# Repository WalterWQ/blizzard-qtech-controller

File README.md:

# Blizzard QTech replacement controller

An open-source replacement main board for the **SUN (Snap-on) Blizzard QTech2** vehicle air-conditioning service machine.

The original controller (NXP LPC2148) failed in my machine: it powered up and clicked its relays, but the display only showed blocks and the buttons did nothing. Every other part of the machine — valves, compressor, vacuum pump, scale, sensors — still worked. Rather than scrap a working machine for one dead board, I designed a new controller from scratch that plugs into the original wiring harness.

> ⚠️ **Mains voltage.** The power board switches 230 V AC to the compressor, heater and valves. Only build, test or install it if you are competent to work on mains equipment. Disconnect the supply before touching anything. The machine also handles pressurised refrigerant — follow F-gas rules.

> Not affiliated with, endorsed by or supported by Snap-on or SUN. "SUN", "Snap-on" and "Blizzard" are used only to describe what this board is compatible with.

| Controller board (v3, 4-layer) | Power & relay board (v1.1, 2-layer) |
|---|---|
|  |  |

## How it's built

The design is split across **two boards joined by a 26-way ribbon cable**, so the low-voltage logic and the mains switching are kept apart. Either board can be repaired or replaced on its own.

```
                 ┌──────────────────────────┐   ribbon (J30)   ┌───────────────────────────┐
  keypad ───────►│     CONTROLLER BOARD     │◄────────────────►│   POWER & RELAY BOARD     │──► 10 × solenoid valves
  LCD    ◄───────│  ESP32-S3, sensors, I/O  │  relay drive,    │  230 V in, fused outputs  │──► compressor, vac pump
  sensors ──────►│  watchdog, RTC, FRAM     │  12 V, SAFE_EN,  │  transformer, 12 V / 5 V  │──► tank heater, fan
  printer ◄──────│                          │  E-stop, HP sw.  │  relays + varistors       │◄── E-stop, HP switch
                 └──────────────────────────┘                  └───────────────────────────┘
```

### Controller board (v3)

4-layer, 180 × 125 mm.

| Function | Part |
|---|---|
| Microcontroller | ESP32-S3-WROOM-1 (N8 or N16R8) — Wi-Fi, USB-C programming with ESD protection |
| Display | Original 14-pin HD44780 character LCD, via a 74HCT245 level shifter; backlight on a MOSFET |
| Keypad | Original keypad, scanned through an MCP23017 I/O expander |
| Pressure | 5 inputs for 0.5–4.5 V transducers (high side, low side, 2 × manifold, spare), each with TVS protection and a jumper-selectable sensor supply |
| Temperature | Tank NTC thermistor |
| Refrigerant scale | NAU7802 24-bit load-cell ADC |
| Current sensing | 2 × 3.5 mm jacks for CT clamps (compressor, vacuum pump) |
| Monitoring | 12 V and 5 V rail monitors, leak sensor — 3 × ADS1115 16-bit ADCs |
| Storage | MB85RC256V FRAM (32 KB) for settings and logs |
| Clock | DS3231M real-time clock with CR2032 backup |
| Safety | TPS3823 hardware watchdog AND-ed with a GPIO to produce `SAFE_EN` — if the firmware hangs, every output drops out |
| Printer | Original printer port, RS-232 (MAX3232) or TTL, jumper selectable |
| Extras | Buzzer, WS2812B status LED, second MCP23017 for expansion |

### Power & relay board (v1.1)

2-layer, 272 × 198 mm, 1 oz copper.

| Function | Detail |
|---|---|
| Mains input | EMI filter choke, X2/Y2 safety capacitors |
| Supplies | Hahn UI39 PCB transformer (reused from the original board) → bridge rectifiers → LM2937 12 V linear and LM2596 5 V buck regulators |
| Fusing | Separate 5×20 mm fuses for the transformer (T125 mA), valves (T2 A), motors (T6.3 A) and heater (T2 A); resettable fuses on the low-voltage side |
| Valve outputs | 10 × 230 V outputs for the Parker YB14 solenoid coils (14 W), each with a varistor |
| Motor outputs | Compressor (1/3 HP), vacuum pump and fan, with larger varistors |
| Heater output | 230 V, 230 W tank heater (optional parts — leave out if the machine has no heater) |
| Relays | 12 V coil relays driven by 2 × ULN2803A, with an LED per output. Footprints for Omron G2RL, plus the original Panasonic JW1FSN / ALZ22B12 relays reused from the old board |
| Safety inputs | E-stop and high-pressure switch (both normally closed) |
| Wiring | 7.62 mm mains screw terminals, labelled for each valve and motor |

Bills of materials: [controller](hardware/controller-board/BOM.csv) · [power board](hardware/power-board/BOM.csv) · [cable and extras](hardware/BOM_extras.csv)

## Repository layout

```
firmware/
  bench-test/AC_Controller_Test/   Bench-test firmware for the controller board
hardware/
  controller-board/                KiCad 10 project, BOM, gerbers (fabrication/), 1:1 fit-check print
  power-board/                     KiCad 10 project, BOM, gerbers, custom footprints and 3D models
  BOM_extras.csv                   Ribbon cable, jumpers and other loose parts
docs/images/                       Board renders
```

Open the `.kicad_pro` files in **KiCad 10** or newer. The gerber zips in each `fabrication/` folder can be uploaded to JLCPCB as they are.

## Bench-test firmware

[`firmware/bench-test`](firmware/bench-test/AC_Controller_Test/AC_Controller_Test.ino) checks a freshly built controller board on its own, powered from USB-C — no power board or mains needed. It uses no external libraries.

On power-up it runs automatic tests and shows the result on the LCD and status LED:

- Finds every I²C device (I/O expanders, ADCs, load-cell ADC, FRAM, RTC)
- FRAM write/read-back and boot counter
- RTC ticking and temperature
- 5 V, 12 V and sensor supply rails
- Load-cell ADC, Wi-Fi scan

Then a serial menu for hands-on tests: live sensor readings, keypad mapping, walking each relay output, backlight/buzzer/LED, the watchdog and `SAFE_EN` cut-out, printer-port loopback, load-cell readings and setting the clock.

**Arduino IDE setup:** board *ESP32S3 Dev Module*, *USB CDC On Boot: Enabled*, flash and PSRAM to match your module. Full steps are at the top of the sketch.

## Status

| Part | Status |
|---|---|
| Controller board v3 | ✅ Built and hand-soldered |
| Bench-test firmware | ✅ Written |
| Power & relay board v1.1 | 🛠️ Design finished, gerbers ready |
| Machine control firmware | 🔜 Next |

## Licence

- Firmware (`firmware/`): [MIT](LICENSE)
- Hardware (`hardware/`): [CERN-OHL-P v2](LICENSE-HARDWARE)

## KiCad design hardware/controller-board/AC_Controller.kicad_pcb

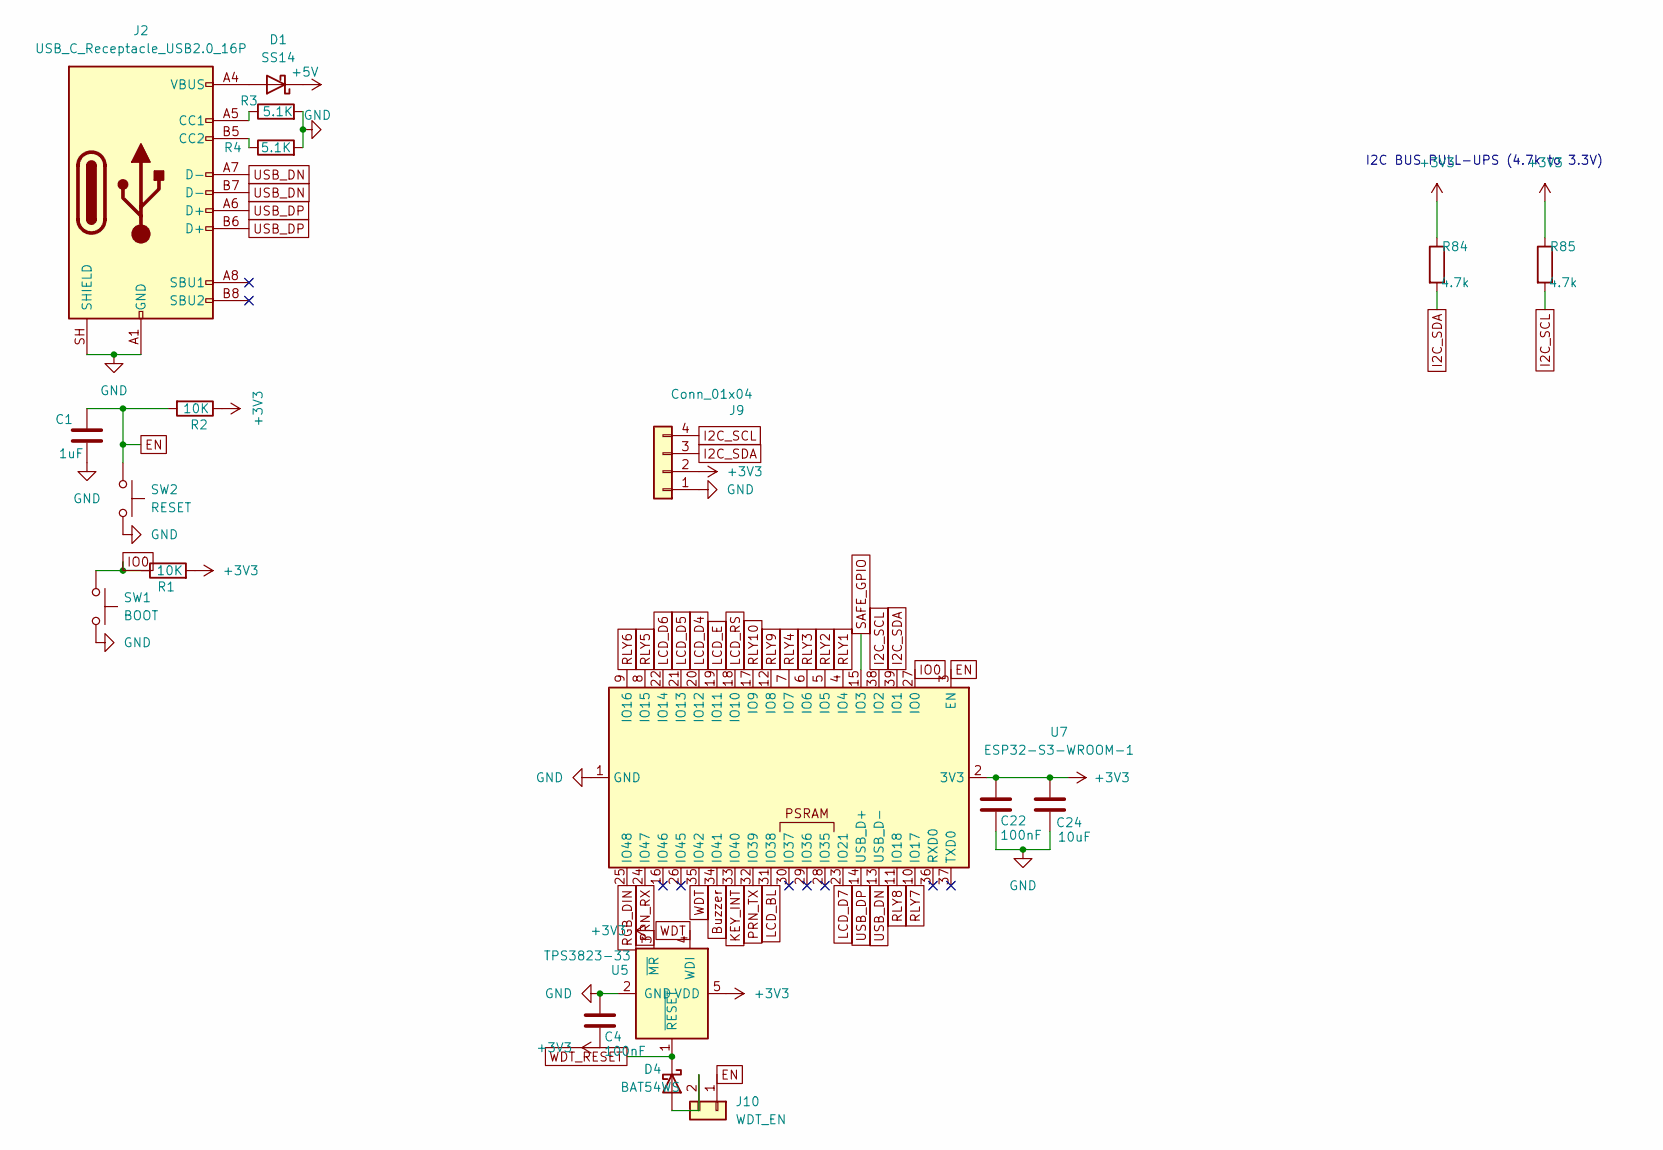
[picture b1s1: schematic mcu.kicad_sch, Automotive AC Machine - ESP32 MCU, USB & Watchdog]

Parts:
C1: 1uF; C_0805_2012Metric
C4, C22: 100nF; C_0805_2012Metric
C24: 10uF; C_0805_2012Metric
D1: SS14; D_SMA
D4: BAT54WS; D_SOD-323
J2: USB_C_Receptacle_USB2.0_16P; USB_C_Receptacle_HRO_TYPE-C-31-M-12
J9: Conn_01x04; PinHeader_1x04_P2.54mm_Vertical
J10: WDT_EN; PinHeader_1x02_P2.54mm_Vertical
R1, R2: 10K; R_0805_2012Metric
R3, R4: 5.1K; R_0805_2012Metric
R84, R85: 4.7k; R_0805_2012Metric
SW1: BOOT; SW_PUSH_6mm
SW2: RESET; SW_PUSH_6mm
U5: TPS3823-33; SOT-23-5
U7: ESP32-S3-WROOM-1

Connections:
+3V3: C4.2, C22.1, C24.1, J9.2, R1.2, R2.1, R84.1, R85.1, U5.3 (~MR), U5.5 (VDD), U7.2 (3V3); also elsewhere on the board
+5V: D1.1 (K); also elsewhere on the board
Buzzer: U7.34 (IO41); also elsewhere on the board
EN: C1.1, J10.1, R2.2, SW2.1, U7.3 (EN)
GND: C1.2, C4.1, C22.2, C24.2, J2.A1 (GND), J2.A12 (GND), J2.B1 (GND), J2.B12 (GND), J2.SH (SHIELD), J9.1, R3.2, R4.2, SW1.2, SW2.2, U5.2 (GND), U7.1 (GND), U7.40 (GND), U7.41 (GND); also elsewhere on the board
I2C_SCL: J9.4, R85.2, U7.38 (IO2); also elsewhere on the board
I2C_SDA: J9.3, R84.2, U7.39 (IO1); also elsewhere on the board
IO0: R1.1, SW1.1, U7.27 (IO0)
KEY_INT: U7.33 (IO40); also elsewhere on the board
LCD_BL: U7.31 (IO38); also elsewhere on the board
LCD_D4: U7.20 (IO12); also elsewhere on the board
LCD_D5: U7.21 (IO13); also elsewhere on the board
LCD_D6: U7.22 (IO14); also elsewhere on the board
LCD_D7: U7.23 (IO21); also elsewhere on the board
LCD_E: U7.19 (IO11); also elsewhere on the board
LCD_RS: U7.18 (IO10); also elsewhere on the board
unnamed: D1.2 (A), J2.A4 (VBUS), J2.A9 (VBUS), J2.B4 (VBUS), J2.B9 (VBUS)
unnamed: D4.2 (A), J10.2
unnamed: J2.A5 (CC1), R3.1
unnamed: J2.B5 (CC2), R4.1
PRN_RX: U7.24 (IO47); also elsewhere on the board
PRN_TX: U7.32 (IO39); also elsewhere on the board
RGB_DIN: U7.25 (IO48); also elsewhere on the board
RLY1: U7.4 (IO4); also elsewhere on the board
RLY2: U7.5 (IO5); also elsewhere on the board
RLY3: U7.6 (IO6); also elsewhere on the board
RLY4: U7.7 (IO7); also elsewhere on the board
RLY5: U7.8 (IO15); also elsewhere on the board
RLY6: U7.9 (IO16); also elsewhere on the board
RLY7: U7.10 (IO17); also elsewhere on the board
RLY8: U7.11 (IO18); also elsewhere on the board
RLY9: U7.12 (IO8); also elsewhere on the board
RLY10: U7.17 (IO9); also elsewhere on the board
SAFE_GPIO: U7.15 (IO3); also elsewhere on the board
USB_DN: J2.A7 (D-), J2.B7 (D-), U7.13 (USB_D-); also elsewhere on the board
USB_DP: J2.A6 (D+), J2.B6 (D+), U7.14 (USB_D+); also elsewhere on the board
WDT: U5.4 (WDI), U7.35 (IO42)
WDT_RESET: D4.1 (K), U5.1 (~RESET); also elsewhere on the board

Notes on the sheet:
I2C BUS PULL-UPS (4.7k to 3.3V)

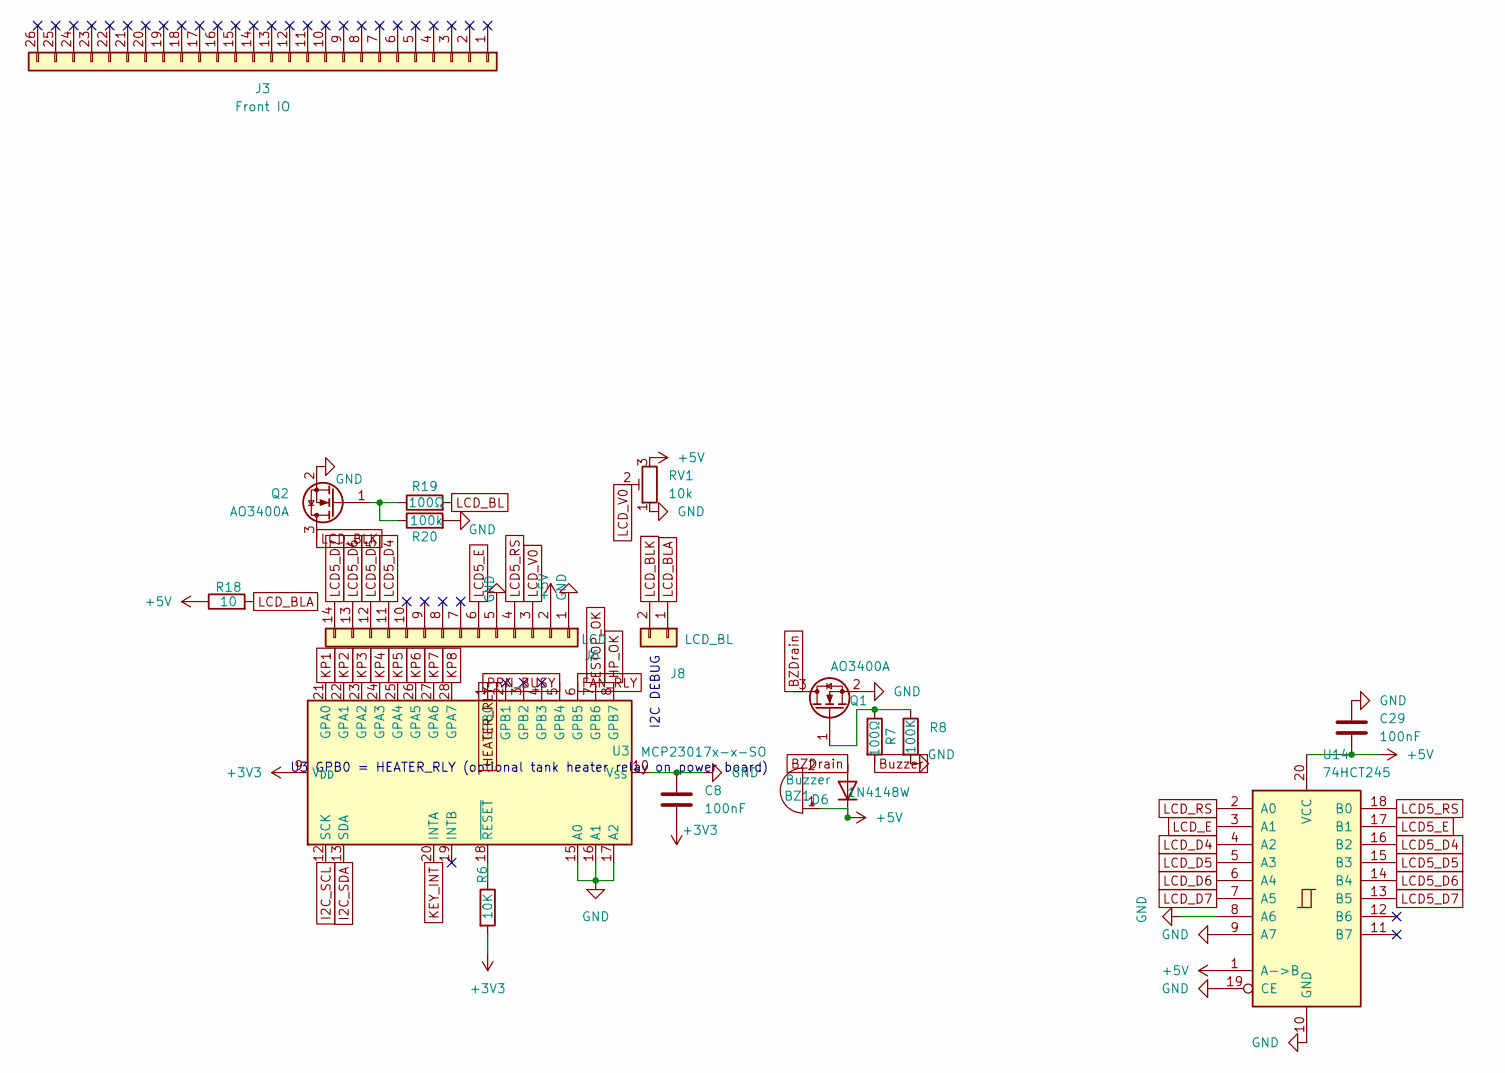
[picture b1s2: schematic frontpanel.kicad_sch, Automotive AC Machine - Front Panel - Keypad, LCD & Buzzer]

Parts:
BZ1: Buzzer; Buzzer_12x9.5RM7.6
C8, C29: 100nF; C_0805_2012Metric
D6: 1N4148W; D_SOD-123
J3: Front IO; PinHeader_1x26_P2.54mm_Vertical
J6: LCD; PinHeader_1x14_P2.54mm_Vertical
J8: LCD_BL; PinHeader_1x02_P2.54mm_Vertical
Q1, Q2: AO3400A; SOT-23
R6: 10K; R_0805_2012Metric
R7, R19: 100Ω; R_0805_2012Metric
R8: 100K; R_0805_2012Metric
R18: 10; R_0805_2012Metric
R20: 100k; R_0805_2012Metric
RV1: 10k; Potentiometer_Bourns_3296W_Vertical
U3: MCP23017x-x-SO; SOIC-28W_7.5x17.9mm_P1.27mm
U14: 74HCT245; SOIC-20W_7.5x12.8mm_P1.27mm

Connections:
+3V3: C8.1, R6.2, U3.9 (V_{DD}); also elsewhere on the board
+5V: BZ1.1 (+), C29.1, D6.1 (K), J6.2, R18.1, RV1.3, U14.1 (A->B), U14.20 (VCC); also elsewhere on the board
BZDrain: BZ1.2 (-), D6.2 (A), Q1.3 (D)
Buzzer: R7.2; also elsewhere on the board
ESTOP_OK: U3.7 (GPB6); also elsewhere on the board
FAN_RLY: U3.6 (GPB5); also elsewhere on the board
GND: C8.2, C29.2, J6.1, J6.5, Q1.2 (S), Q2.2 (S), R8.2, R20.2, RV1.1, U3.10 (V_{SS}), U3.15 (A0), U3.16 (A1), U3.17 (A2), U14.8 (A6), U14.9 (A7), U14.10 (GND), U14.19 (CE); also elsewhere on the board
HEATER_RLY: U3.1 (GPB0); also elsewhere on the board
HP_OK: U3.8 (GPB7); also elsewhere on the board
I2C_SCL: U3.12 (SCK); also elsewhere on the board
I2C_SDA: U3.13 (SDA); also elsewhere on the board
KEY_INT: U3.20 (INTA); also elsewhere on the board
KP1: U3.21 (GPA0); also elsewhere on the board
KP2: U3.22 (GPA1); also elsewhere on the board
KP3: U3.23 (GPA2); also elsewhere on the board
KP4: U3.24 (GPA3); also elsewhere on the board
KP5: U3.25 (GPA4); also elsewhere on the board
KP6: U3.26 (GPA5); also elsewhere on the board
KP7: U3.27 (GPA6); also elsewhere on the board
KP8: U3.28 (GPA7); also elsewhere on the board
LCD5_D4: J6.11, U14.16 (B2)
LCD5_D5: J6.12, U14.15 (B3)
LCD5_D6: J6.13, U14.14 (B4)
LCD5_D7: J6.14, U14.13 (B5)
LCD5_E: J6.6, U14.17 (B1)
LCD5_RS: J6.4, U14.18 (B0)
LCD_BL: R19.2; also elsewhere on the board
LCD_BLA: J8.1, R18.2
LCD_BLK: J8.2, Q2.3 (D)
LCD_D4: U14.4 (A2); also elsewhere on the board
LCD_D5: U14.5 (A3); also elsewhere on the board
LCD_D6: U14.6 (A4); also elsewhere on the board
LCD_D7: U14.7 (A5); also elsewhere on the board
LCD_E: U14.3 (A1); also elsewhere on the board
LCD_RS: U14.2 (A0); also elsewhere on the board
LCD_V0: J6.3, RV1.2
unnamed: Q1.1 (G), R7.1, R8.1
unnamed: Q2.1 (G), R19.1, R20.1
unnamed: R6.1, U3.18 (~RESET)
PRN_BUSY: U3.5 (GPB4); also elsewhere on the board

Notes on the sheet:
I2C DEBUG
U3 GPB0 = HEATER_RLY (optional tank heater relay on power board)

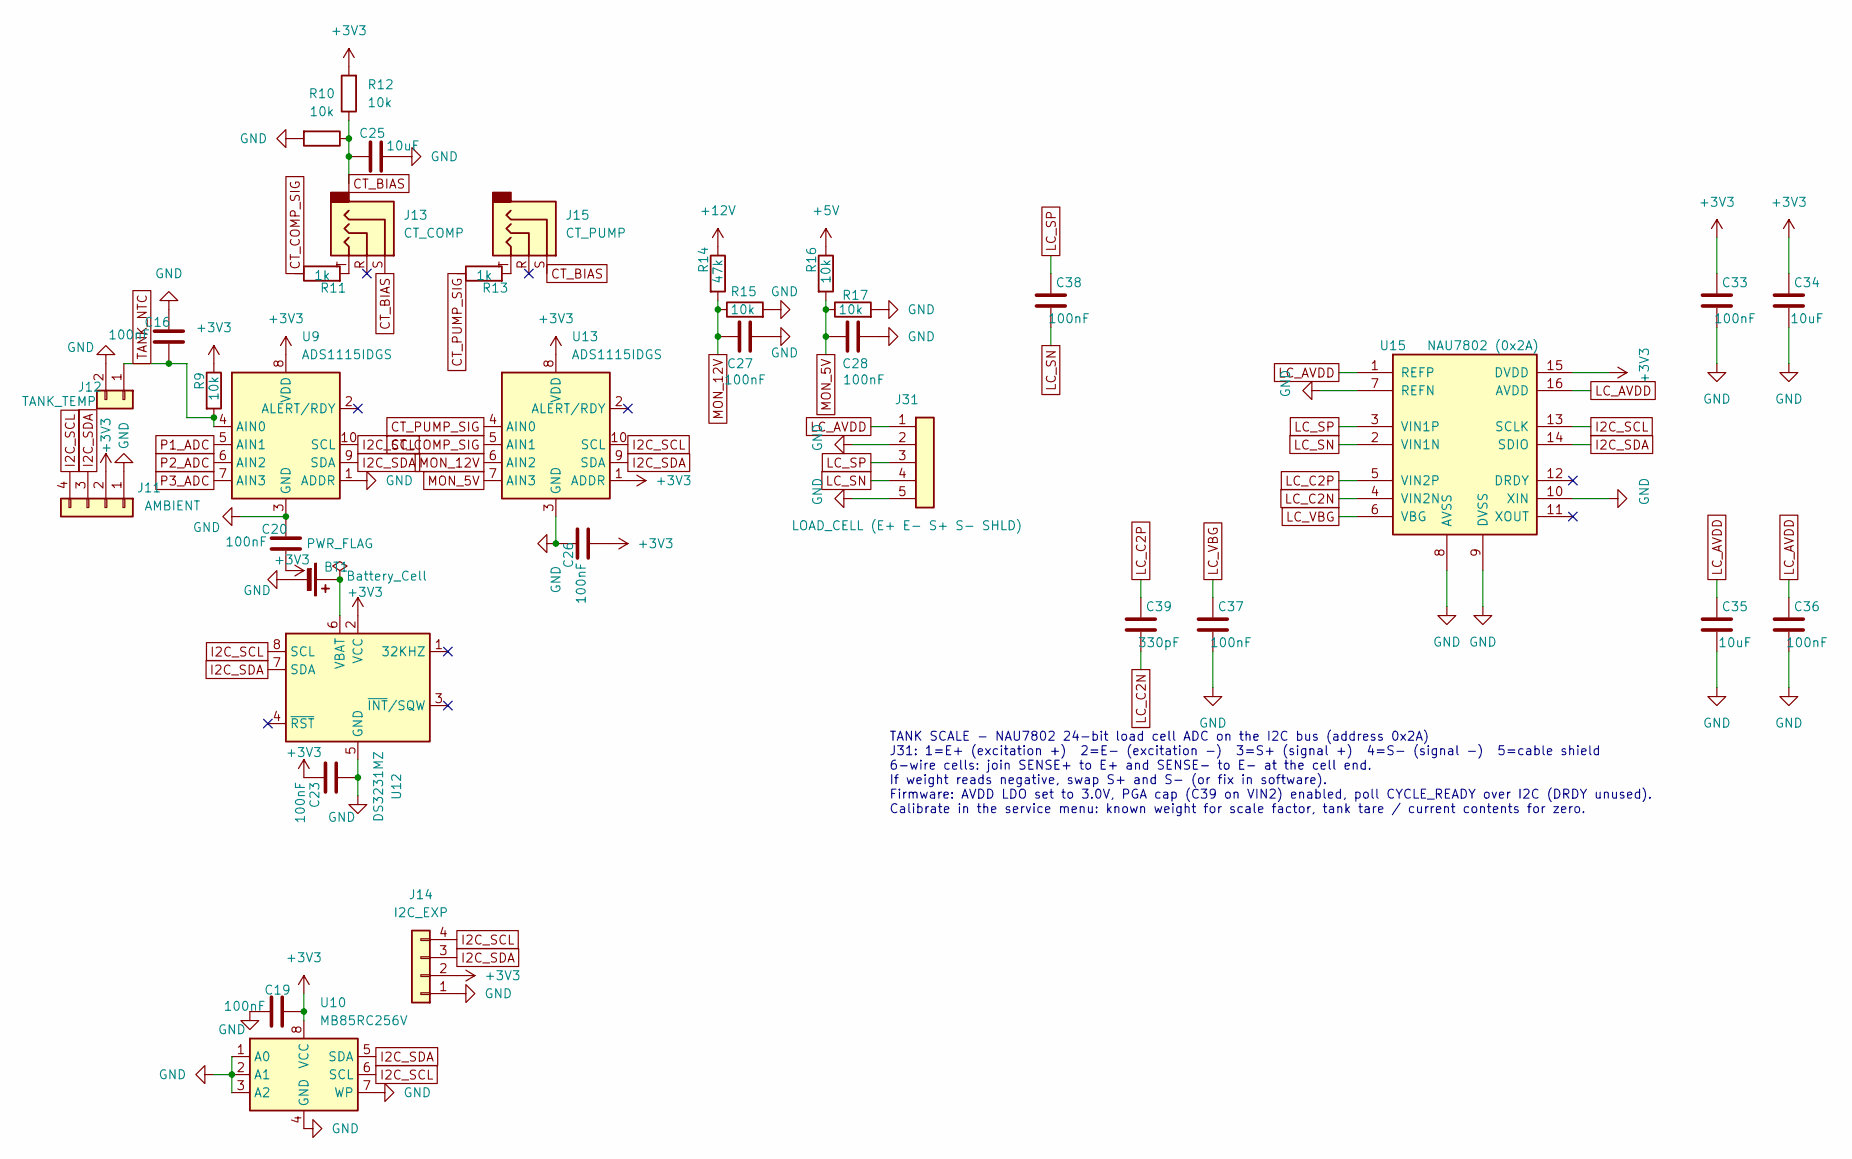
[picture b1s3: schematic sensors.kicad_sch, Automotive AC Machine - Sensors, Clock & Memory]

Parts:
BT1: Battery_Cell; BatteryHolder_Keystone_1058_1x2032
C16, C19, C20, C23, C26, C27, C28, C33, C36, C37, C38: 100nF; C_0805_2012Metric
C25, C34, C35: 10uF; C_0805_2012Metric
C39: 330pF; C_0805_2012Metric
J11: AMBIENT; PinHeader_1x04_P2.54mm_Vertical
J12: TANK_TEMP; TerminalBlock_Phoenix_MKDS-1,5-2-5.08_1x02_P5.08mm_Horizont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
J13: CT_COMP; Jack_3.5mm_CUI_SJ1-3533NG_Horizontal
J14: I2C_EXP; PinHeader_1x04_P2.54mm_Vertical
J15: CT_PUMP; Jack_3.5mm_CUI_SJ1-3533NG_Horizontal
J31: LOAD_CELL (E+ E- S+ S- SHLD); TerminalBlock_Phoenix_MKDS-1,5-5-5.08_1x05_P5.08mm_Horizont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
R9, R10, R12, R15, R16, R17: 10k; R_0805_2012Metric
R11, R13: 1k; R_0805_2012Metric
R14: 47k; R_0805_2012Metric
U9, U13: ADS1115IDGS; TSSOP-10_3x3mm_P0.5mm
U10: MB85RC256V; SOIC-8_3.9x4.9mm_P1.27mm
U12: DS3231MZ; SOIC-8_3.9x4.9mm_P1.27mm
U15: NAU7802 (0x2A); SOIC-16_3.9x9.9mm_P1.27mm

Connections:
+3V3: C19.2, C20.2, C23.2, C26.2, C33.1, C34.1, J11.2, J14.2, R9.1, R12.2, U9.8 (VDD), U10.8 (VCC), U12.2 (VCC), U13.1 (ADDR), U13.8 (VDD), U15.15 (DVDD); also elsewhere on the board
+5V: R16.1; also elsewhere on the board
+12V: R14.1; also elsewhere on the board
CT_BIAS: C25.1, J13.S, J15.S, R10.1, R12.1
CT_COMP_SIG: R11.1, U13.5 (AIN1); also elsewhere on the board
CT_PUMP_SIG: R13.1, U13.4 (AIN0); also elsewhere on the board
GND: BT1.2 (-), C16.1, C19.1, C20.1, C23.1, C25.2, C26.1, C27.2, C28.2, C33.2, C34.2, C35.2, C36.2, C37.2, J11.1, J12.2, J14.1, J31.2, J31.5, R10.2, R15.2, R17.2, U9.1 (ADDR), U9.3 (GND), U10.1 (A0), U10.2 (A1), U10.3 (A2), U10.4 (GND), U10.7 (WP), U12.5 (GND), U13.3 (GND), U15.7 (REFN), U15.8 (AVSS), U15.9 (DVSS), U15.10 (XIN); also elsewhere on the board
I2C_SCL: J11.4, J14.4, U9.10 (SCL), U10.6 (SCL), U12.8 (SCL), U13.10 (SCL), U15.13 (SCLK); also elsewhere on the board
I2C_SDA: J11.3, J14.3, U9.9 (SDA), U10.5 (SDA), U12.7 (SDA), U13.9 (SDA), U15.14 (SDIO); also elsewhere on the board
LC_AVDD: C35.1, C36.1, J31.1, U15.1 (REFP), U15.16 (AVDD)
LC_C2N: C39.2, U15.4 (VIN2N)
LC_C2P: C39.1, U15.5 (VIN2P)
LC_SN: C38.2, J31.4, U15.2 (VIN1N)
LC_SP: C38.1, J31.3, U15.3 (VIN1P)
LC_VBG: C37.1, U15.6 (VBG)
MON_5V: C28.1, R16.2, R17.1, U13.7 (AIN3)
MON_12V: C27.1, R14.2, R15.1, U13.6 (AIN2)
unnamed: BT1.1 (+), U12.6 (VBAT)
unnamed: J13.T, R11.2
unnamed: J15.T, R13.2
P1_ADC: U9.5 (AIN1); also elsewhere on the board
P2_ADC: U9.6 (AIN2); also elsewhere on the board
P3_ADC: U9.7 (AIN3); also elsewhere on the board
TANK_NTC: C16.2, J12.1, R9.2, U9.4 (AIN0); also elsewhere on the board

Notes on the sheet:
TANK SCALE - NAU7802 24-bit load cell ADC on the I2C bus (address 0x2A) J31: 1=E+ (excitation +) 2=E- (excitation -) 3=S+ (signal +) 4=S- (signal -) 5=cable shield 6-wire cells: join SENSE+ to E+ and SENSE- to E- at the cell end. If weight reads negative, swap S+ and S- (or fix in software). Firmwa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

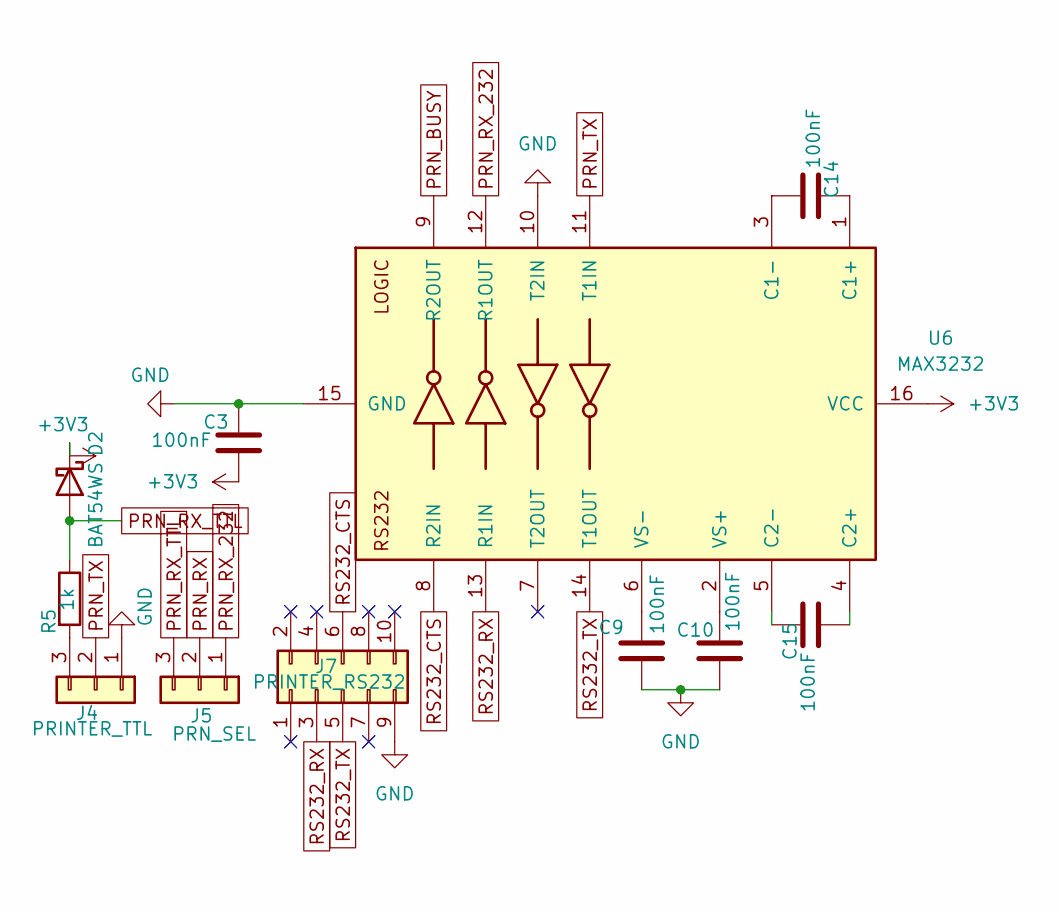
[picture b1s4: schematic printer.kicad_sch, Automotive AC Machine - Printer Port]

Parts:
C3, C9, C10, C14, C15: 100nF; C_0805_2012Metric
D2: BAT54WS; D_SOD-323
J4: PRINTER_TTL; PinHeader_1x03_P2.54mm_Vertical
J5: PRN_SEL; PinHeader_1x03_P2.54mm_Vertical
J7: PRINTER_RS232; IDC-Header_2x05_P2.54mm_Vertical
R5: 1k; R_0805_2012Metric
U6: MAX3232; SOIC-16_3.9x9.9mm_P1.27mm

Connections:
+3V3: C3.2, D2.1 (K), U6.16 (VCC); also elsewhere on the board
GND: C3.1, C9.2, C10.2, J4.1, J7.9, U6.10 (T2IN), U6.15 (GND); also elsewhere on the board
unnamed: J4.3, R5.2
unnamed: C14.1, U6.1 (C1+)
unnamed: C14.2, U6.3 (C1-)
unnamed: C15.2, U6.4 (C2+)
unnamed: C15.1, U6.5 (C2-)
unnamed: C10.1, U6.2 (VS+)
unnamed: C9.1, U6.6 (VS-)
PRN_BUSY: U6.9 (R2OUT); also elsewhere on the board
PRN_RX: J5.2; also elsewhere on the board
PRN_RX_232: J5.1, U6.12 (R1OUT)
PRN_RX_TTL: D2.2 (A), J5.3, R5.1
PRN_TX: J4.2, U6.11 (T1IN); also elsewhere on the board
RS232_CTS: J7.6, U6.8 (R2IN)
RS232_RX: J7.3, U6.13 (R1IN)
RS232_TX: J7.5, U6.14 (T1OUT)

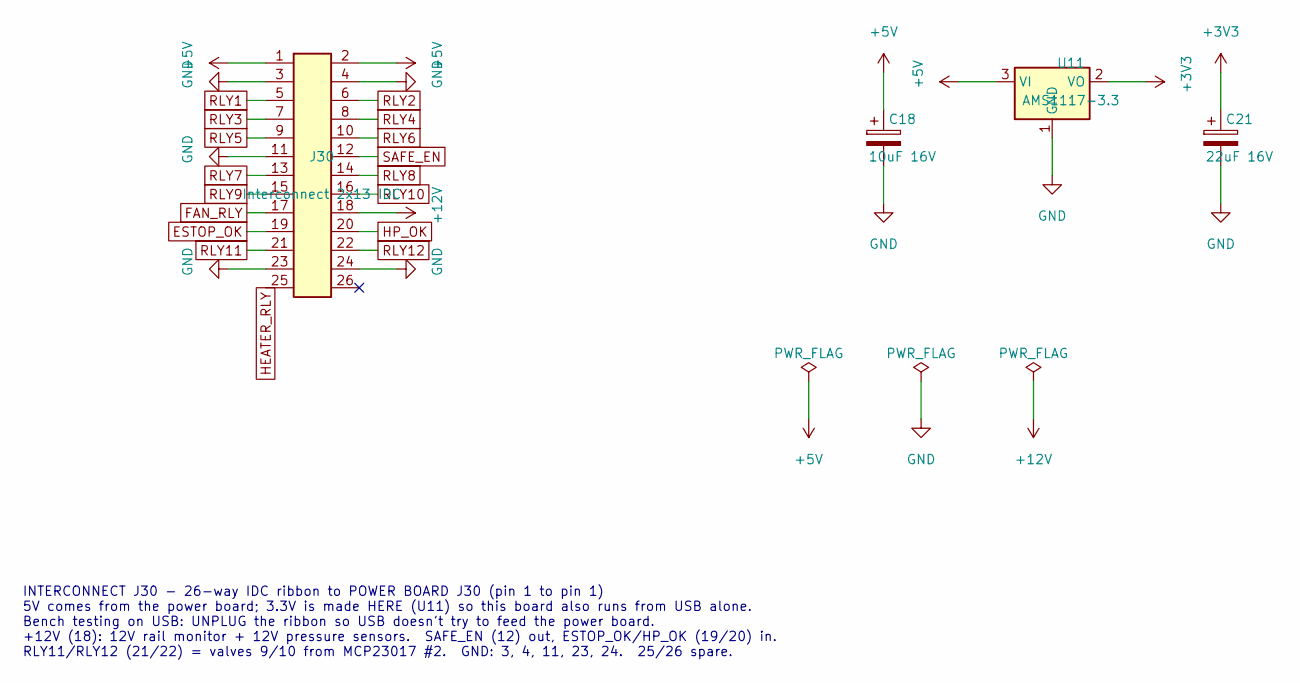
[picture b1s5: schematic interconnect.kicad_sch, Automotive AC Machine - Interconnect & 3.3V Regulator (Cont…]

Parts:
C18: 10uF 16V; CP_Radial_D5.0mm_P2.00mm
C21: 22uF 16V; CP_Radial_D5.0mm_P2.00mm
J30: Interconnect 2x13 IDC; IDC-Header_2x13_P2.54mm_Vertical
U11: AMS1117-3.3; SOT-223-3_TabPin2

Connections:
+3V3: C21.1, U11.2 (VO); also elsewhere on the board
+5V: C18.1, J30.1, J30.2, U11.3 (VI); also elsewhere on the board
+12V: J30.18; also elsewhere on the board
ESTOP_OK: J30.19; also elsewhere on the board
FAN_RLY: J30.17; also elsewhere on the board
GND: C18.2, C21.2, J30.3, J30.4, J30.11, J30.23, J30.24, U11.1 (GND); also elsewhere on the board
HEATER_RLY: J30.25; also elsewhere on the board
HP_OK: J30.20; also elsewhere on the board
RLY1: J30.5; also elsewhere on the board
RLY2: J30.6; also elsewhere on the board
RLY3: J30.7; also elsewhere on the board
RLY4: J30.8; also elsewhere on the board
RLY5: J30.9; also elsewhere on the board
RLY6: J30.10; also elsewhere on the board
RLY7: J30.13; also elsewhere on the board
RLY8: J30.14; also elsewhere on the board
RLY9: J30.15; also elsewhere on the board
RLY10: J30.16; also elsewhere on the board
RLY11: J30.21; also elsewhere on the board
RLY12: J30.22; also elsewhere on the board
SAFE_EN: J30.12; also elsewhere on the board

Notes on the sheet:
INTERCONNECT J30 - 26-way IDC ribbon to POWER BOARD J30 (pin 1 to pin 1) 5V comes from the power board; 3.3V is made HERE (U11) so this board also runs from USB alone. Bench testing on USB: UNPLUG the ribbon so USB doesn't try to feed the power board. +12V (18): 12V rail monitor + 12V pressure sens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

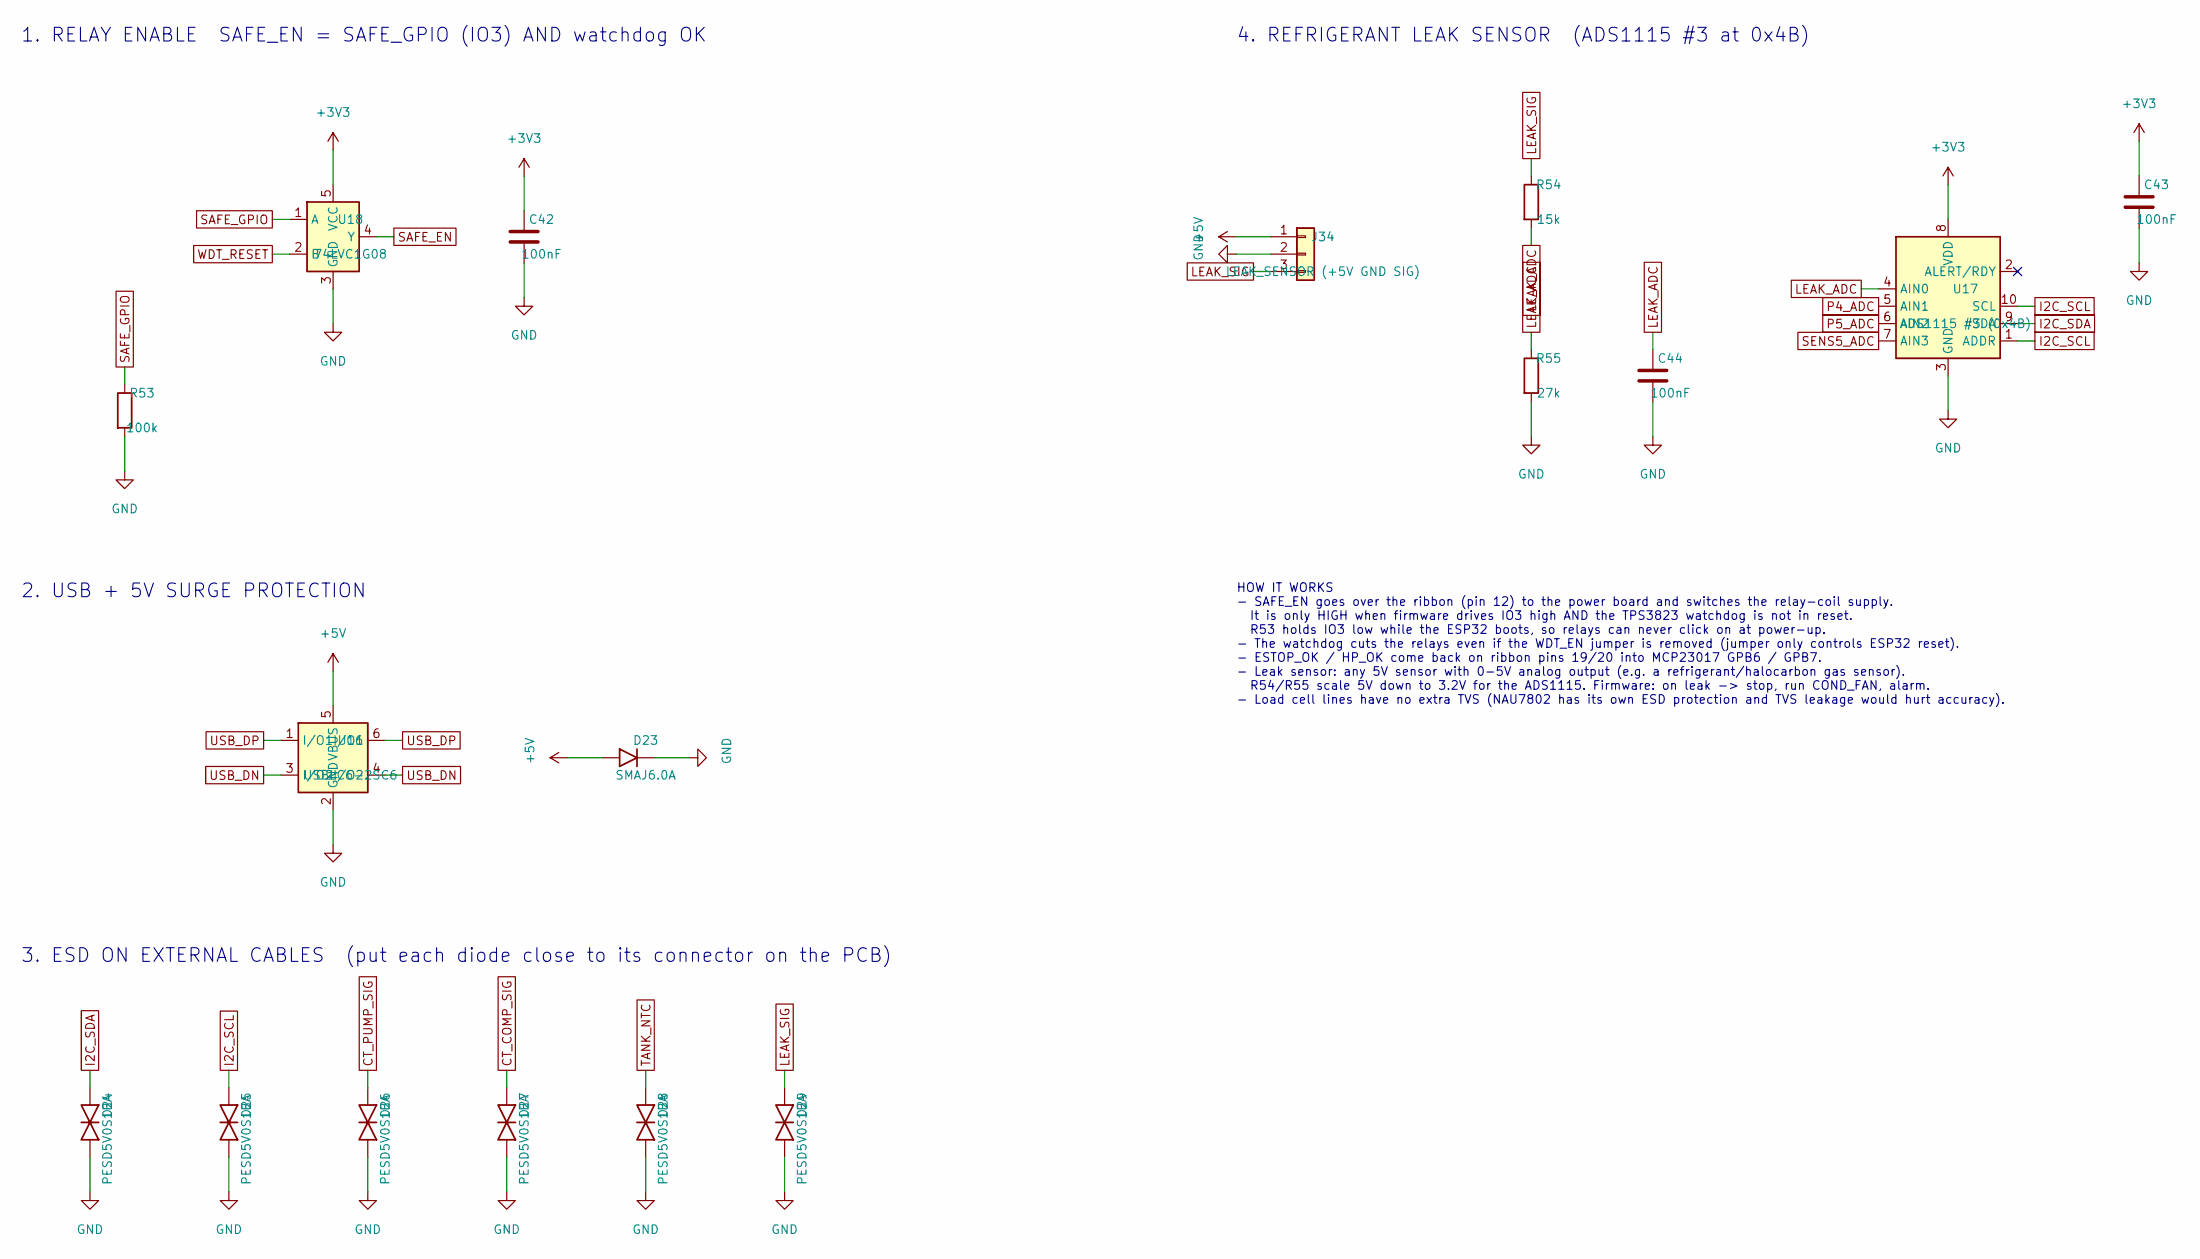
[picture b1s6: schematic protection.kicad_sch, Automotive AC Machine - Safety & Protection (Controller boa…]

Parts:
C42, C43, C44: 100nF; C_0805_2012Metric
D23: SMAJ6.0A; D_SMA
D24, D25, D26, D27, D28, D29: PESD5V0S1BA; D_SOD-323
J34: LEAK_SENSOR (+5V GND SIG); TerminalBlock_Phoenix_MKDS-1,5-3-5.08_1x03_P5.08mm_Horizont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
R53: 100k; R_0805_2012Metric
R54: 15k; R_0805_2012Metric
R55: 27k; R_0805_2012Metric
U16: USBLC6-2SC6; SOT-23-6
U17: ADS1115 #3 (0x4B); TSSOP-10_3x3mm_P0.5mm
U18: 74LVC1G08; SOT-23-5

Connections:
+3V3: C42.1, C43.1, U17.8 (VDD), U18.5 (VCC); also elsewhere on the board
+5V: D23.1 (K), J34.1, U16.5 (VBUS); also elsewhere on the board
CT_COMP_SIG: D27.1 (A1); also elsewhere on the board
CT_PUMP_SIG: D26.1 (A1); also elsewhere on the board
GND: C42.2, C43.2, C44.2, D23.2 (A), D24.2 (A2), D25.2 (A2), D26.2 (A2), D27.2 (A2), D28.2 (A2), D29.2 (A2), J34.2, R53.2, R55.2, U16.2 (GND), U17.3 (GND), U18.3 (GND); also elsewhere on the board
I2C_SCL: D25.1 (A1), U17.1 (ADDR), U17.10 (SCL); also elsewhere on the board
I2C_SDA: D24.1 (A1), U17.9 (SDA); also elsewhere on the board
LEAK_ADC: C44.1, R54.2, R55.1, U17.4 (AIN0)
LEAK_SIG: D29.1 (A1), J34.3, R54.1
P4_ADC: U17.5 (AIN1); also elsewhere on the board
P5_ADC: U17.6 (AIN2); also elsewhere on the board
SAFE_EN: U18.4 (Y); also elsewhere on the board
SAFE_GPIO: R53.1, U18.1 (A); also elsewhere on the board
SENS5_ADC: U17.7 (AIN3); also elsewhere on the board
TANK_NTC: D28.1 (A1); also elsewhere on the board
USB_DN: U16.3 (I/O2), U16.4 (I/O2); also elsewhere on the board
USB_DP: U16.1 (I/O1), U16.6 (I/O1); also elsewhere on the board
WDT_RESET: U18.2 (B); also elsewhere on the board

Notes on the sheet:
1. RELAY ENABLE SAFE_EN = SAFE_GPIO (IO3) AND watchdog OK
2. USB + 5V SURGE PROTECTION
3. ESD ON EXTERNAL CABLES (put each diode close to its connector on the PCB)
4. REFRIGERANT LEAK SENSOR (ADS1115 #3 at 0x4B)
HOW IT WORKS - SAFE_EN goes over the ribbon (pin 12) to the power board and switches the relay-coil supply. It is only HIGH when firmware drives IO3 high AND the TPS3823 watchdog is not in reset. R53 holds IO3 low while the ESP32 boots, so relays can never click on at power-up. - The watchdog cuts 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
